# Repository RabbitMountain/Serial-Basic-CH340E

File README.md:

# Serial-Basic-CH340E
Serial Basic CH340E and USBC

This is based on the SparkFun Serial Basic Breakout is an easy-to-use USB-to-Serial adapter based on the CH340E and takes advantage of the handy USB-C connector. With USB-C you can get up to three times the power delivery over the previous USB generation at 1.5A and and also solves the universally frustrating dilemma of plugging a USB cable in correctly, because it’s reversible! The Serial Basic works with 5V and 3.3V systems and possesses the capability to auto install on most operating systems without the need for additional drivers. The Serial Basic uses the CH340E IC to quickly and easily convert serial signals to USB.

The pinout of the Serial Basic mimics the common DTR/RXI/TXO/VCC/CTS/GND pinout found on hundreds of FTDI-to-USB derivatives. It can also be used as a general serial device for debugging (such as with a GPS module). There is a jumper on the rear of the board that controls the output voltage on the VCC pin. By default, the board outputs 3.3V and has 3.3V signals. Changing this jumper to 5V will cause the board to output 5V on the VCC pin with 5V signals.

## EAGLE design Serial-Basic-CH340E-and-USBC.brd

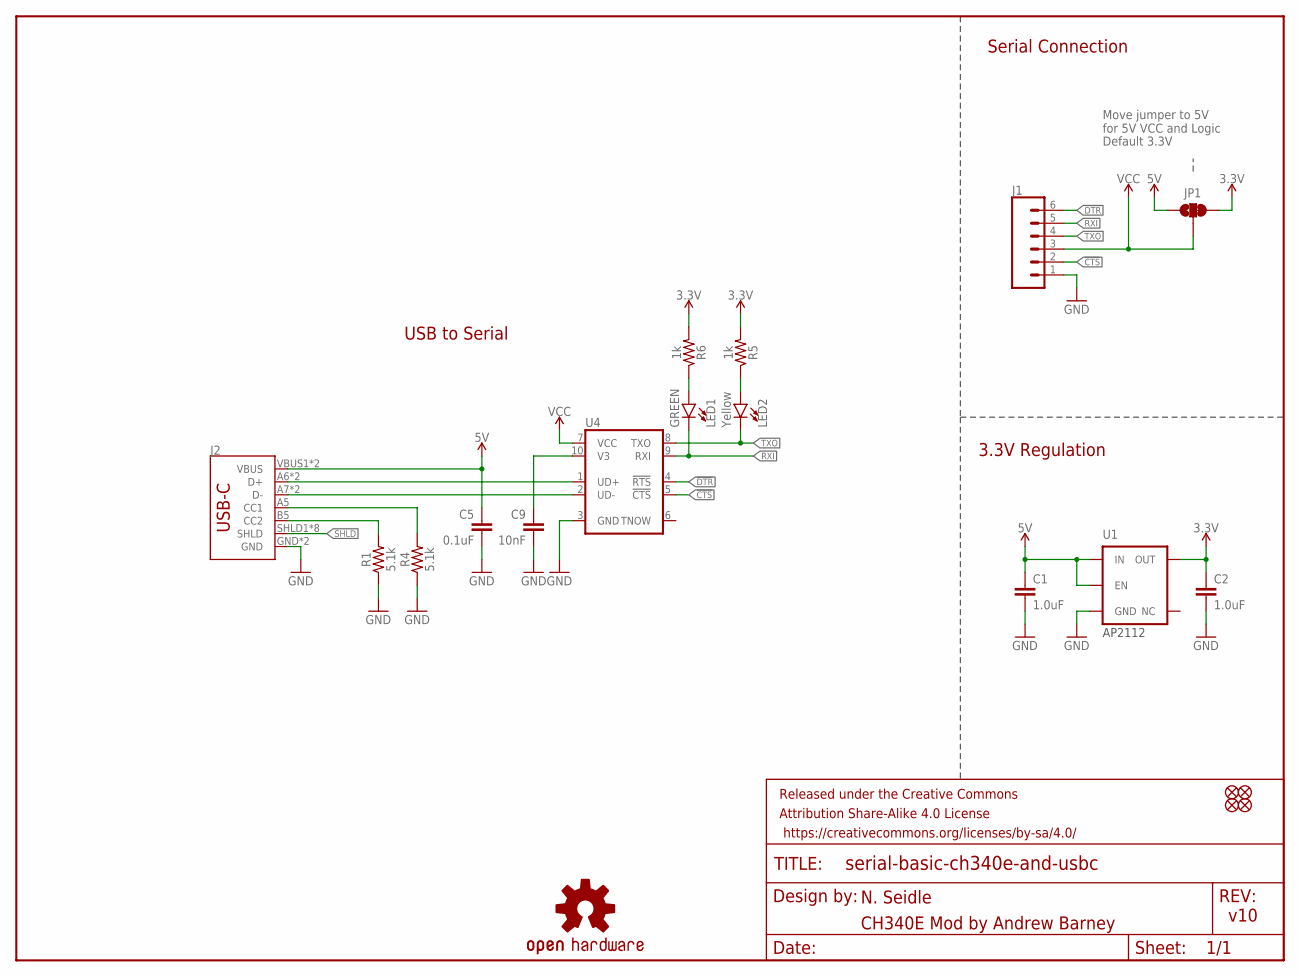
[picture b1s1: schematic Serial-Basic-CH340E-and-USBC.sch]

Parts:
C1, C2: 1.0uF; 0603
C5: 0.1uF; 0603
C9: 10nF; 0603
FRAME1: FRAME-LETTER; CREATIVE_COMMONS
J1: CONN_06SMD-FEMALE-V2; 1X06-SMD-FEMALE
J2: USB_C16PIN; USB-C-16P
JP1: JUMPER-SMT_3_1-NC_TRACE_SILK; SMT-JUMPER_3_1-NC_TRACE_SILK
JP3, JP4, JP5, JP6: FIDUCIAL1X2; FIDUCIAL-1X2
LED1: GREEN; LED-0603
LED2: Yellow; LED-0603
LOGO1: OSHW-LOGOS; OSHW-LOGO-S
R1, R4: 5.1k; 0603
R5, R6: 1k; 0603
U1: 3.3V; SOT23-5
U4: CH340E_MSOP10; MSOP10

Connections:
3.3V: C2.1, JP1.3, R5.2, R6.2, U1.5 (OUT)
5V: C1.1, C5.1, J2.VBUS1 (VBUS), J2.VBUS2 (VBUS), JP1.1, U1.1 (IN), U1.3 (EN)
!CTS: J1.2, U4.5 (!CTS)
!DTR: J1.6, U4.4 (!RTS)
CC1: J2.A5 (CC1), R4.2
CC2: J2.B5 (CC2), R1.2
D+: J2.A6 (D+), J2.B6 (D+), U4.1 (UD+)
D-: J2.A7 (D-), J2.B7 (D-), U4.2 (UD-)
GND: C1.2, C2.2, C5.2, C9.2, J1.1, J2.GND, J2.GND2 (GND), R1.1, R4.1, U1.2 (GND), U4.3 (GND)
unnamed: C9.1, U4.10 (V3)
unnamed: LED1.A, R6.1
unnamed: LED2.A, R5.1
RXI: J1.5, LED1.C, U4.9 (RXI)
SHLD: J2.SHLD1 (SHLD), J2.SHLD2 (SHLD), J2.SHLD3 (SHLD), J2.SHLD4 (SHLD), J2.SHLD5 (SHLD), J2.SHLD6 (SHLD), J2.SHLD7 (SHLD), J2.SHLD8 (SHLD)
TXO: J1.4, LED2.C, U4.8 (TXO)
VCC: J1.3, JP1.2, U4.7 (VCC)

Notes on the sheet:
Default 3.3V
v10
USB to Serial
3.3V Regulation
N. Seidle
Move jumper to 5V for 5V VCC and Logic
Serial Connection
AP2112
CH340E Mod by Andrew Barney

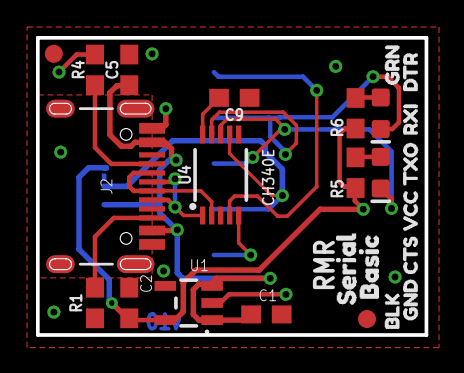
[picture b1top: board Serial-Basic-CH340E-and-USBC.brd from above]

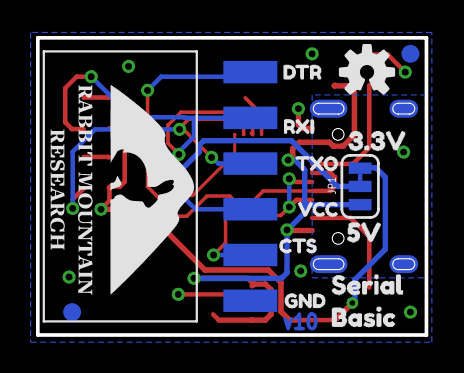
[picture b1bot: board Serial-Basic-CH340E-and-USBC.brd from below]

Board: 2 copper layers, 21.6 x 16.5 mm, 42 parts (16 on the bottom side), 16 nets.

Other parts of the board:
U$1, U$14: CTS1
U$2: 3#3V8
U$3: 5V9
U$4, U$9: SERIAL0
U$5, U$12: TXO0
U$6, U$13: VCC2
U$7, U$11: BASIC1
U$8, U$18: DTR0
U$10, U$21: RXI1
U$15, U$19: GND5
U$16: RMR-SIT-8MM
U$17: BLK6
U$20: GRN7

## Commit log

2020-12-19 Add files via upload
    This is based on the SparkFun Serial Basic Breakout is an easy-to-use USB-to-Serial adapter based on the CH340E and takes advantage of the handy USB-C connector. With USB-C you can get up to three ti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
    The pinout of the Serial Basic mimics the c

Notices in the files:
parts and their libraries:
SparkFun-Aesthetics: Licensing: CC v3.0 Share-Alike You are welcome to use this library for commercial purposes.
SparkFun-Aesthetics: Released under the Creative Commons Attribution Share-Alike 4.0 License
SparkFun-Aesthetics: https://creativecommons.org/licenses/by-sa/4.0
